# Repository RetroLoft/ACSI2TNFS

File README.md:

# ACSI2TNFS

A Raspberry Pi Pico 2 W on the **ACSI** (hard disk) port of an Atari. To the Atari it is
a hard disk; behind it are your network and a micro SD card.

It works with every 16-bit Atari that has an ACSI port: **ST, STE, Mega ST, Mega STE
and TT**. The Falcon has no ACSI port (it has SCSI), so ACSI2TNFS cannot be used there.

ACSI2TNFS gives the Atari:

- **Network drives:** folders on a **TNFS** server (a PC, a NAS, a Raspberry Pi) that
  the Atari sees as hard disk partitions, readable and writable.
- **SD card drives:** folders on a micro SD card in the adapter, also as hard disk
  partitions.
- **Internet:** with the STinG TCP/IP stack the Atari gets its own IP address on your
  Wi-Fi network: ping, FTP, web pages.
- **The right time:** the adapter gets the time from the internet and sets the Atari's
  clock.

All of these are optional: use only what you need. A small drive in the Pico's flash,
the **settings drive**, always comes with it: it holds the configuration program and the
tools.

> Status: working on real hardware: ST with TOS 1.02/1.04, Mega STE (TOS 2.06, HDDRIVER),
> TT (TOS 3.06, AHDI) and EmuTOS.

> [!IMPORTANT]
> ## MEGA STE AND TT: SET THE ADAPTER TO THE FIRST FREE ACSI ID
>
> **A new adapter uses ACSI id 6. On a Mega STE or a TT the machine does not see it there.**
>
> - **TT** (tested with AHDI): only ACSI id **0** is asked at start-up. Its own hard disk
>   is SCSI, so use **id 0**.
> - **Mega STE:** the internal hard disk adapter is on id 0, so use **id 1**. With
>   HDDRIVER also switch id 1 on in HDDRUTIL.
> - In general: the lowest id that no other device on the ACSI port uses.
>
> Set it with the USB console (key `0`–`7`) or `ACSITNFS.PRG` → *Config → More*, then
> restart the Atari. See [docs/ADAPTER.md](docs/ADAPTER.md#acsi-id).

## What you need

- The ACSI2TNFS board with a **Raspberry Pi Pico 2 W**: `v2` plugs straight into the
  Atari, `v2-cable` connects with a flat cable to a Lotharek DB19 adapter and has a
  pass-through connector. See [hardware/README.md](hardware/README.md).
- An Atari with an ACSI port and **TOS 1.02 or later**, or EmuTOS. TOS 1.0 does not
  see the adapter.
- For the network functions: a **2.4 GHz** Wi-Fi network.
- For SD card drives: a micro SD card, formatted on a PC as FAT32 (or exFAT).
- A USB cable for the Pico: it powers the adapter and gives a console on your PC.

## Getting started

1. **Firmware.** Download `acsi2tnfs.uf2` from
   [Releases](https://github.com/RetroLoft/ACSI2TNFS/releases). Hold the Pico's BOOTSEL
   button while you plug it into a PC, and copy the file onto the drive that appears.
   The Pico restarts and prepares its settings drive. (To build it yourself: see
   [docs/DEVELOPMENT.md](docs/DEVELOPMENT.md).)
2. **Connect** the adapter to the Atari's ACSI port and power the Pico over USB.
   Switch the Atari on. Without another hard disk you see `ACSI2TNFS v…` and
   `[OK] Drives installed: C:`.
3. **Show the settings drive on the desktop.** Select the floppy A: icon, *Options →
   Install Disk Drive*, letter `C`, *Install*, then *Options → Save Desktop*.
4. **Configure.** Start `ACSITNFS.PRG` on the settings drive: *Config* for Wi-Fi (network
   name, password, country) with *More* for the clock and the ACSI id, and the drive list
   for TNFS and SD drives (see below). *Save*; the Pico restarts and the Atari with it.

From then on the Atari boots with its drives and the right time.

## The settings drive

The first drive of the adapter lives in the Pico's flash (about 1 MB). Which letter it
gets depends on what else is connected:

- **No other hard disk:** the adapter boots with its own driver and the settings drive
  is **C:**, the boot drive, with your AUTO folder and DESKTOP.INF.
- **You already have a hard disk:** its driver boots and the adapter's drives follow
  after your own partitions. With a hard disk with C: and D:, the settings drive is E:.

On the settings drive:

| File | |
|---|---|
| `ACSITNFS.PRG` | the configuration program: Wi-Fi, TNFS and SD drives, network clock, ACSI id |
| `STINGINS.TOS` | installs STinG for internet on the Atari (below) |
| `NETCLOCK.PRG` | sets the Atari's clock from the network (for the AUTO folder, below) |
| `ACSI_NET.STX` | the STinG driver for the adapter (STINGINS.TOS installs it) |
| `README.TXT` | a short manual |

These files come with the firmware and are read-only. Your own files on the drive stay
when you update the firmware.

## Network drives (TNFS)

A TNFS drive shows a folder on a TNFS server as a hard disk partition. Setting up a TNFS
server is easy: [tnfsd](https://github.com/spectrumero/tnfsd) runs on Linux, macOS,
Windows and a Raspberry Pi; give it a folder and it serves that folder.

TNFS has no passwords and no encryption: run your server **only in your own network**
and do not open it to the internet.

In `ACSITNFS.PRG`, per drive: the server (name or IP address), the folder on the server
and the drive letter. More, and how writing works: [docs/TNFS.md](docs/TNFS.md).

## SD card drives

An SD drive shows a **folder** on the micro SD card in the adapter, e.g. `/ATARI`, as a
hard disk partition. It is not a disk image or a real partition: the adapter translates
the Atari's sector reads and writes into normal files on the card. Put the card in a PC
and you see the same files.

SD drives work without Wi-Fi. With a card in the adapter, TNFS drives also use it as a
write cache: writing to the network gets about six times faster.
More: [docs/SDCARD.md](docs/SDCARD.md).

## Drive letters and hard disk drivers

Next to the settings drive the adapter offers up to **three** TNFS or SD drives.
`ACSITNFS.PRG` has eight slots: the first three that are switched on are used.

Most TOS versions need a hard disk driver to use ACSI drives. Which one loads decides the
drive letters:

| Driver | Letters |
|---|---|
| **The adapter's own driver** (no other hard disk) | the settings drive is C:; TNFS and SD drives get the letters chosen in `ACSITNFS.PRG` (D: to P:). A letter that is taken gives the next free one |
| **AHDI** | assigns letters in order, after your own partitions; the letters in `ACSITNFS.PRG` are not used |
| **HDDRIVER** | assigns letters itself, also in order; HDDRUTIL has its own settings for letters and ACSI ids |
| **EmuTOS** | mounts the adapter with its own ACSI driver as C:, D:, … in order |

With AHDI, HDDRIVER and EmuTOS the adapter's driver does not load, so it does not set the
clock: use `NETCLOCK.PRG` (below). Details per driver and machine:
[docs/ADAPTER.md](docs/ADAPTER.md#booting).

## Internet on the Atari (STinG)

The adapter passes network traffic between the Atari and your Wi-Fi network. The Atari
runs the [STinG](https://github.com/th-otto/STinG) TCP/IP stack (freeware, for TOS); the
driver `ACSI_NET.STX` connects STinG to the adapter.

`STINGINS.TOS` on the settings drive installs everything (STinG 1.26 with TCP.STX 1.41).
Start it and answer its questions:

1. **The drive to install on:** your boot drive, almost always C: (it suggests it).
2. If STinG is already there: **1** changes only the network settings, **2** installs
   everything again. In doubt, choose 2.
3. **Atari IP address:** a **free** address in your network: not the adapter's own, and
   outside the range your router hands out (DHCP).
4. **Subnet mask:** almost always `255.255.255.0`.
5. **Gateway:** your router's IP address. On a Windows PC `ipconfig` shows it as
   *Default Gateway*.
6. **DNS server:** usually the router's address too.

The installer suggests mask, gateway and DNS from the adapter's own Wi-Fi settings.
Confirm, and it installs the files. Restart the Atari: STinG is on the network, without
XControl.

Test with `C:\STING\TOOLS\PING.PRG` to your router. Small STinG programs, e.g. a web
page viewer: [Network tools for the Atari ST](https://github.com/RetroLoft/atari-net-tools).
More, with what the installer writes and troubleshooting: [docs/NETWORK.md](docs/NETWORK.md).

## The clock (NETCLOCK.PRG)

With its own driver the adapter sets the Atari's clock at start-up (switch it on in
`ACSITNFS.PRG` → *Config → More*, with your time zone). With AHDI or HDDRIVER that driver
does not load: copy `NETCLOCK.PRG` into the AUTO folder of your boot drive. It waits for
the adapter's Wi-Fi and the time server (up to 30 s each, ESC skips) and sets the clock.

The time zone is a fixed offset from UTC: change it by hand for summer time.

## Limitations

- **8.3 file names only.** The Atari knows names of at most 8 characters plus a 3-letter
  extension. Longer names on the server or the card are shortened: `LONGFILENAME.TXT`
  shows as `LONGFILE.TXT`, or `LONGFI~1.TXT` when that name is taken. Names that start
  with a dot are hidden.
- **16 MB per drive.** Every TNFS and SD drive is a FAT16 partition of 16 MB, whatever
  the size of the folder behind it. A single file larger than that cannot be shown.
- **The room per drive can run out**, and folders then show up empty: see
  [Empty folders on a network or SD drive](#empty-folders-on-a-network-or-sd-drive).
- **Number of files:** at most 511 entries in the root of a drive and 254 in a folder;
  and about 2400 files and folders in all the folders the Atari has opened since its
  reset, shared by the drives (a drive that is used much takes what the others leave).
- **Changes on the server or the card** made by others (a PC) are seen after the Atari
  reads that folder again: after an Atari reset, or console `N`. Changes made by the
  Atari itself are seen at once.
- **Writing goes in two steps.** The Atari writes sectors; about a second after it
  stops, the adapter turns them into files on the server or card. A large file takes a
  few seconds to arrive on a TNFS server: wait a moment before you switch the adapter
  off.
- **Speed:** reading from a TNFS drive goes at network speed; writing is slower (much
  faster with an SD card as write cache). STinG reaches about 70 KB/s.
- **Drive letters stop at P:** (TOS knows 16 drives).
- **TOS 1.x with several drives:** put `FOLDR100.PRG` (from Atari's AHDI) in your AUTO
  folder, or TOS runs out of folder memory ("use FOLDR100.PRG").
- **Wi-Fi:** 2.4 GHz only (the Pico 2 W's radio).

## Empty folders on a network or SD drive

**Why it happens.** The Atari expects a hard disk with a FAT, a fixed table of where every
file lies. A network or SD drive has no such table: the adapter makes it up while you use
the drive. The first time the Atari opens a folder, the adapter reads that folder from
the server or the card and gives each file in it a place in the drive's 16 MB. That
place stays reserved until the drive starts afresh. The room for one session is limited:

- **16 MB of file space** per drive: every file in every folder you opened counts,
  whether you use it or not;
- **about 2400 files and folders**, shared by all network and SD drives;
- **only the part of the FAT that TOS has not read yet:** TOS keeps the FAT sectors it
  has read in memory, so the adapter cannot add new files there.

**What fills it up quickly**

- **Show Info** (*File → Show Info*) on a network or SD drive. To count the files and
  bytes, TOS opens **every folder** of the drive, down to the last subfolder. On a large
  server this uses up the room of the drive in one go, and every folder that did not
  fit is remembered by TOS as empty. Show Info on a single small folder is fine.
- Programs that ask for the free space of a drive: TOS then reads the whole FAT.
- Browsing through many folders full of large files (disk images, for example).

**What you see.** Folders you open after that are empty or show only part of their
files. The USB console (`n`, and the log) says "some skipped".

**What to do** depends on the hard disk driver:

| Driver | What happens | What you do |
|---|---|---|
| **The adapter's own driver** | after 2 seconds without disk activity the adapter starts the drive afresh and reports a media change; TOS reads the drive again | close the folder and open it again (TOS 2.06: or press Esc) |
| **HDDRIVER** | the same, once console `M` is on: the adapter then reports itself as a removable unit, and HDDRIVER asks for media changes | press `M` on the USB console once (it is stored), then reset the Atari once. Without `M`: reset the Atari |
| **AHDI** | nothing: AHDI does not hear of media changes | reset the Atari. **Leave `M` off:** with AHDI it makes TOS read the whole FAT again and again, and folders stay empty |
| **EmuTOS** (its built-in driver) | nothing: EmuTOS does not hear of media changes | reset the Atari (`M` makes no difference) |

A reset of the Atari always starts every drive afresh, with any driver. A single folder
whose files together are larger than 16 MB always shows only part of its files.

## Documentation

| | |
|---|---|
| [docs/TNFS.md](docs/TNFS.md) | Network drives: TNFS servers, writing, what to keep in mind |
| [docs/SDCARD.md](docs/SDCARD.md) | SD card drives and the write cache |
| [docs/NETWORK.md](docs/NETWORK.md) | Internet with STinG: the installer, IP address, programs, limits |
| [docs/ADAPTER.md](docs/ADAPTER.md) | ACSI id, booting, USB console, system files, troubleshooting |
| [hardware/README.md](hardware/README.md) | The boards `v2` and `v2-cable`, pin map, case |
| [docs/DEVELOPMENT.md](docs/DEVELOPMENT.md) | Building, repository layout, ACSI protocol, test tools |
| `ACSI_NET-ontwerp.md`, `project-notities.md` | Design and project notes (Dutch) |

## Credits

- Configuration program: the ACSI build of
  [SideTNFS-Config](https://github.com/RetroLoft/SideTNFS-Config).
- `ACSI_NET.STX` follows the structure of
  [USB_NET.STX (usbsting)](https://github.com/czietz/usbsting) by Roger Burrows and
  Christian Zietz (GPL-2+), and the frame bridge follows
  [PicoWifi](https://github.com/czietz/picowifi).
- STinG by Peter Rottengatter and Ronald Andersson (freeware); TCP.STX 1.41 by Christian
  Zietz ([chzsoft/sting](https://github.com/chzsoft/sting)). `STINGINS.TOS` carries
  them unchanged (`atari/install/sting/`).
- SD card: [FatFs](http://elm-chan.org/fsw/ff/) by ChaN.

## License

Copyright (C) 2025-2026 Frank Beentjes.

GNU General Public License, version 3 or (at your option) any later version: see
[LICENSE](LICENSE).

- `atari/sting/` (`ACSI_NET.STX`) contains code after USB_NET.STX and is GPL-2.0-or-later
  (`atari/sting/LICENSE`); `atari/sting/include/` holds headers from the STinG developer kit.
- The firmware is built with the Raspberry Pi Pico SDK (BSD-3-Clause), lwIP (BSD),
  FatFs (BSD-style, `third_party/fatfs`) and the `cyw43-driver` for the Wi-Fi chip, which
  Raspberry Pi licenses for use with its own microcontrollers only
  (`lib/cyw43-driver/LICENSE.RP` in the SDK).

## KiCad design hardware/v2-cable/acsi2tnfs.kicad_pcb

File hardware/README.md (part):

# ACSI2TNFS hardware

There are two boards with the same circuit and pin map, so one firmware fits both. Only
the way they connect to the Atari's ACSI port differs:

- **`v2`** plugs straight into the ACSI port, without a cable.
- **`v2-cable`** connects through a Lotharek DB19 adapter and a 20-wire flat cable, and
  can pass the ACSI bus on to another device, such as Lotharek's UltraSatan.

## Which one?

| | `v2` | `v2-cable` |
|---|---|---|
| Connection | plugs straight into the ACSI port | 20-wire flat cable to a Lotharek DB19 adapter in the ACSI port |
| Where it sits | upright on the back of the Atari, sticking out above it: leds, button and SD card in sight | loose on or behind the Atari |
| Pass-through | no | yes: a second header for another ACSI device, e.g. an UltraSatan |
| Case | none | a 3D-printable case (`v2-cable/case/`) |
| Special parts | 19 WAGO 243-131 pins for the DB19 | a Lotharek adapter (or build `acsi-adapter`) and a flat cable |

| `v2` | `v2-cable` |
|---|---|
|  |  |

*3D views from KiCad. Not every part has a 3D model (the SD socket and the button are
missing).*

## v2: straight into the ACSI port

The DB19 plug is part of the board: 19 loose pins soldered into the board take the place
of a DB19 plug (footprint `ACSI_DB19_Male_WAGO_243-131`). The board stands upright on
the back of the Atari, held by the port, and sticks out above it, so the leds, the
button and the micro SD card are in sight.

- **Pro:** no adapter and no cable needed.
- **Con:** you need the special pins: **WAGO 243-131** solder pins (1.0 mm pins in
  1.2 mm holes), 19 per board. For example from
  [Farnell](https://nl.farnell.com/en-NL/wago/243-131/solder-pin-2mm-pcb-terminal-block/dp/2643506)
  or [RS](https://nl.rs-online.com/web/p/terminal-block-accessories/2885173).
- No pass-through: the board takes the ACSI port.

## v2-cable: with a Lotharek adapter

The board lies loose on or behind the Atari and hangs on a Lotharek DB19 adapter through
a 20-wire flat cable. That adapter comes with Lotharek's
[UltraSatan](https://lotharek.pl/products.php?id=15): if you already have one, this is
the easiest way.

- **J1 "To ACSI"** takes the cable from the adapter. **J2 "ACSI pass-through"** carries
  the same signals on, e.g. to the UltraSatan, which then shares the bus with its own
  ACSI id.
- J1 and J2 are keyed box headers. Their pins are numbered **per row**: 1-10 along the
  row on the side of the key, 11-20 along the other row (footprint
  `IDC-Header_2x10_P2.54mm_Vertical_NR_PER_ROW`).
- So **pin n on the board is ACSI pin n**, because the adapter puts DB19 pins 1-10 on one
  row of its header and 11-19 on the other. This is **not** the usual IDC numbering
  (1 and 2 opposite each other): a standard 2x10 footprint would mix up the signals.
- The cable is a straight 20-wire flat cable with an IDC socket at each end, keyed the
  same way at both ends.

| Pin | Signal | Pin | Signal |
|---|---|---|---|
| 1-8 | DATA0-DATA7 | 11, 13, 15, 17 | GND |
| 9 | /CS | 12 | /RESET |
| 10 | /IRQ | 14 | /ACK |
| | | 16 | A1 |
| | | 18 | R/W |
| | | 19 | /DRQ |
| | | 20 | not used |

### No Lotharek adapter? Make one

`acsi-adapter` is the same adapter as a KiCad project: the DB19 of `v2` (the same special
pins) wired 1:1 to the IDC20 box header of `v2-cable`, pin 20 not connected. The box
header sits on the side of the wide DB19 row, like on Lotharek's adapter.

### The case

`v2-cable/case/` holds a 3D-printable case: `case.scad` (OpenSCAD) and ready STL files.

- **Bottom** with a flat front panel: the SD socket ends flush with it, the button
  sticks out about 1 mm, and the two 3 mm leds sit in holes. "ACSI2TNFS" is engraved in
  the corner.
- **Two lids:** `lid-vertical` for straight box headers (the rear left corner is open,
  with walls around the headers), `lid-right-angle` for angled box headers (openings in
  the rear wall).
- Two **M2.5 countersunk screws** (about 12 mm) from below, through the bottom and the
  board into plugs of the lid.
- Print the bottom as it is and the lid upside down (as in the STL files). No supports
  needed.
- **Assembly:** the SD socket and the button go through the front panel. Put the board
  in at the rear, slide it forward until the socket is flush with the panel, then screw
  it down. Trim the pins under the board to about 2.5 mm.
- The lid height is for a Pico on female headers (about 12.5 mm above the board).
  Heights and openings can be changed at the top of `case.scad`.

## Getting a board

Choose your version first, then whether you order the board ready-made or build it
yourself.

### Ordering it assembled

The boards are made for [JLCPCB](https://jlcpcb.com), which makes the board and solders
the SMD parts:

1. In KiCad, make the production files with the plugin
   [Fabrication Toolkit](https://github.com/bennymeg/Fabrication-Toolkit): it writes the
   Gerber zip, `bom.csv` and `positions.csv` into `production/`.
2. At JLCPCB upload the Gerber zip and switch on **PCB Assembly**, top side.
3. **Quantity:** 2, 5 or a multiple of 5. For 2 boards choose a **green** board: other
   colours start at 5.
4. Upload `bom.csv` and `positions.csv`. Parts without an LCSC number in the schematic
   are picked in the BOM step. **U1 and U2** must be the wide SOIC-20 version,
   **74LVC245ADW**, not the small TSSOP (APW).
5. **Check the placement preview:** the rotation of some parts is often wrong. For
   every IC, led and the SD socket the dot at pin 1 of the part must sit on the pin-1
   mark of the footprint; rotate the part in the preview where it does not.
6. The cheapest shipping works fine: boards usually arrive in the Netherlands from China
   in 10 to 14 days.

The through-hole parts (Pico headers, box headers or DB19 pins, button, 3 mm leds) are
easy to solder yourself afterwards, or ask JLCPCB to fit them too.

### Building it yourself

All SMD parts are on the top side and have a pin pitch of 1.1 mm or more, so a
**hotplate** works well:

1. **SMD parts on the hotplate.** Put a tiny dot of solder paste on each pad: a dot is
   enough to solder a pin to its pad. With too much paste neighbouring pins bridge. A
   stencil is not needed.
2. Place the parts with tweezers, heat the board until the paste flows, let it cool.
3. **Through-hole parts** with a normal soldering iron: Pico headers, box headers or
   DB19 pins, button, leds.

Plenty of videos show hotplate soldering. Useful tools: reading glasses or a magnifier,
good light, tweezers, and a **toothpick**: it is not magnetic and good for moving paste
and parts.

### Parts

| Ref | Part | Package | Notes |
|---|---|---|---|
| A1 | Raspberry Pi Pico 2 W | module | on female headers (socket) or soldered |
| U1, U2 | 74LVC245ADW | SOIC-20W | wide SOIC, not TSSOP |
| U3 | 74LS07 | SOIC-14 | |
| Card1 | TF-01A micro SD socket (LCSC C91145) | SMD | push-push |
| R1, R2, R5-R8 | 10k | 0805 | |
| R3, R4 | 470 Ω | 0805 | led resistors |
| C1, C5, C7 | 10 µF | 0805 | |
| C2, C3, C4, C6 | 100 nF | 0805 | |
| SW1 | 6 mm tactile switch, right angle (Alps SKHH footprint) | THT | |
| D1, D2 (`v2`) | led 3 mm: D1 yellow, D2 blue | THT | bent forward |
| D1, D2 / D3, D4 (`v2-cable`) | led 0805 / led 3 mm: D1/D3 yellow, D2/D4 blue | SMD / THT | fit **either** D1 **or** D3, and D2 **or** D4 |
| J1 (`v2`) | 19 × WAGO 243-131 | THT | the DB19 plug |
| J1, J2 (`v2-cable`) | 2x10 box header, 2.54 mm, straight or right angle | THT | the lid of the case depends on it |

## Both boards

- **Raspberry Pi Pico 2 W** on pin headers. The Pico powers the board from USB; the
  ACSI port has no supply pin.
- **U1** 74LVC245: data bus D0-D7, direction (DIR) and enable (/OE) from the Pico.
  **U2** 74LVC245: /CS, /RESET, /ACK, A1 and R/W to the Pico, fixed direction.
  **U3** 74LS07: /IRQ and /DRQ as open-collector outputs.
- **Card1:** micro SD socket on SPI0, with card detect.
- **SW1:** button (hidden mode on/off). **Leds:** D1 disk activity, D2 status (on, blinking
  while hidden); on `v2-cable` D3 and D4 when the 3 mm leds are fitted.

### Design rules learnt the hard way

The Atari's floppy controller shares the ACSI data bus and the /IRQ line, so the board
must keep off them when it is not talking:

- **No pull-ups on /IRQ and /DRQ** to the board's own supply: without USB that supply is
  0 V and the resistors pull the lines low, which upsets the floppy drive. The Atari has
  its own pull-ups.
- **10k pull-up on /OE of U1** (R5): the data bus buffer stays off while the Pico is not
  running (power-up, reset, BOOTSEL).
- **10k pull-ups on the 74LS07 inputs** (R6, R7): a Pico in reset pulls its pins low,
  which would otherwise assert /IRQ and /DRQ.

### Pin map (v2 and v2-cable)

| Pico | Signal | Pico | Signal |
|---|---|---|---|
| GP0 | led D1 (disk activity) | GP16 | /CS |
| GP1 | SD card detect | GP17 | /RESET |
| GP2-GP5 | SD card: CLK, MOSI, MISO, CS | GP18 | /ACK |
| GP6-GP13 | DATA7 ... DATA0 (reversed order) | GP19 | A1 |
| GP14 | DIR of U1 | GP20 | R/W |
| GP15 | /OE of U1 | GP21 | /IRQ (via U3, low = active) |
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
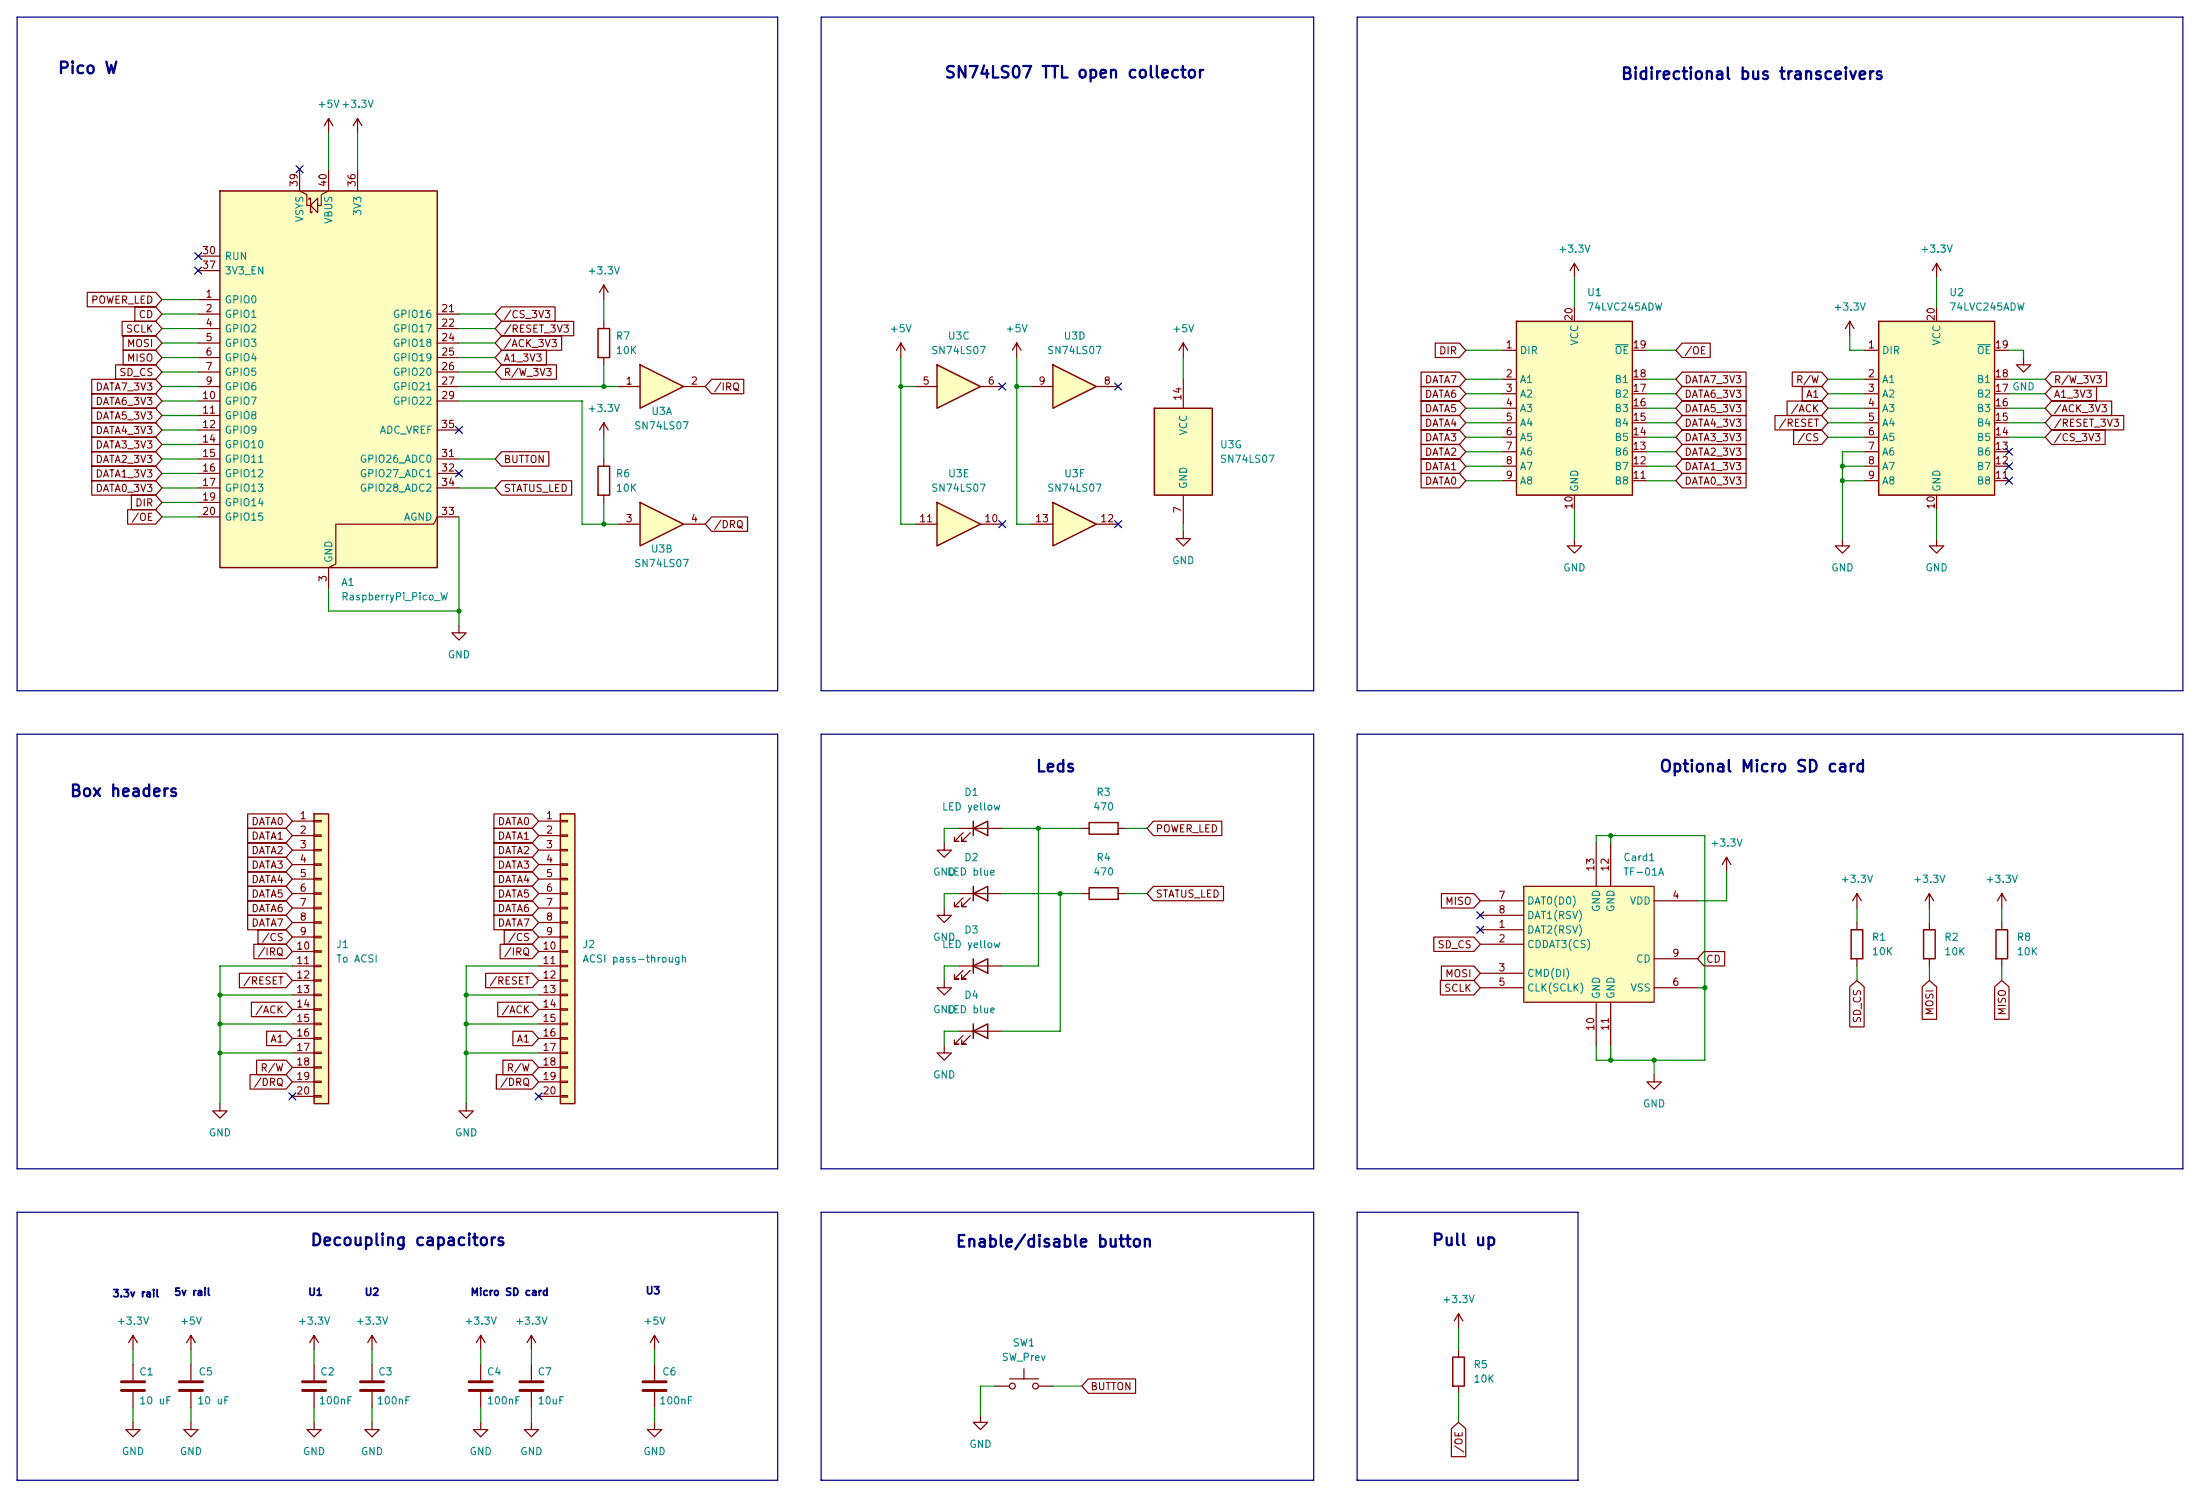
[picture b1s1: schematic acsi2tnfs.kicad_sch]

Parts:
A1: RaspberryPi_Pico_W; RaspberryPi_Pico_Common_THT
C1, C5: 10 uF; C_0805_2012Metric
C2, C3, C4, C6: 100nF; C_0805_2012Metric
C7: 10uF; C_0805_2012Metric
Card1: TF-01A; TF-SMD_TF-01A; MPN TF-01A; LCSC Part C91145
D1: LED yellow; LED_0805_2012Metric
D2: LED blue; LED_0805_2012Metric
D3: LED yellow; LED_D3.0mm
D4: LED blue; LED_D3.0mm
J1: To ACSI; IDC-Header_2x10_P2.54mm_Vertical_NR_PER_ROW
J2: ACSI pass-through; IDC-Header_2x10_P2.54mm_Vertical_NR_PER_ROW
R1, R2, R5, R6, R7, R8: 10K; R_0805_2012Metric
R3, R4: 470; R_0805_2012Metric
SW1: SW_Prev; SW_Tactile_SKHH_Angled
U1, U2: 74LVC245ADW; SOIC-20W_7.5x15.4mm_P1.27mm
U3: SN74LS07; SOIC-14_3.9x8.7mm_P1.27mm

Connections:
+3.3V: A1.36 (3V3), C1.1, C2.1, C3.1, C4.1, C7.1, Card1.4 (VDD), R1.1, R2.1, R5.1, R6.1, R7.1, R8.1, U1.20 (VCC), U2.1 (DIR), U2.20 (VCC)
+5V: A1.40 (VBUS), C5.1, C6.1, U3.5, U3.9, U3.11, U3.13, U3.14 (VCC)
A1: J1.16, J2.16, U2.3 (A2)
A1_3V3: A1.25 (GPIO19), U2.17 (B2)
BUTTON: A1.31 (GPIO26_ADC0), SW1.2
CD: A1.2 (GPIO1), Card1.9 (CD)
DATA0: J1.1, J2.1, U1.9 (A8)
DATA0_3V3: A1.17 (GPIO13), U1.11 (B8)
DATA1: J1.2, J2.2, U1.8 (A7)
DATA1_3V3: A1.16 (GPIO12), U1.12 (B7)
DATA2: J1.3, J2.3, U1.7 (A6)
DATA2_3V3: A1.15 (GPIO11), U1.13 (B6)
DATA3: J1.4, J2.4, U1.6 (A5)
DATA3_3V3: A1.14 (GPIO10), U1.14 (B5)
DATA4: J1.5, J2.5, U1.5 (A4)
DATA4_3V3: A1.12 (GPIO9), U1.15 (B4)
DATA5: J1.6, J2.6, U1.4 (A3)
DATA5_3V3: A1.11 (GPIO8), U1.16 (B3)
DATA6: J1.7, J2.7, U1.3 (A2)
DATA6_3V3: A1.10 (GPIO7), U1.17 (B2)
DATA7: J1.8, J2.8, U1.2 (A1)
DATA7_3V3: A1.9 (GPIO6), U1.18 (B1)
DIR: A1.19 (GPIO14), U1.1 (DIR)
GND: A1.3 (GND), A1.8 (GND), A1.13 (GND), A1.18 (GND), A1.23 (GND), A1.28 (GND), A1.33 (AGND), A1.38 (GND), C1.2, C2.2, C3.2, C4.2, C5.2, C6.2, C7.2, Card1.6 (VSS), Card1.10 (GND), Card1.11 (GND), Card1.12 (GND), Card1.13 (GND), D1.1 (K), D2.1 (K), D3.1 (K), D4.1 (K), J1.11, J1.13, J1.15, J1.17, J2.11, J2.13, J2.15, J2.17, SW1.1, U1.10 (GND), U2.7 (A6), U2.8 (A7), U2.9 (A8), U2.10 (GND), U2.19 (~OE), U3.7 (GND)
MISO: A1.6 (GPIO4), Card1.7 (DAT0(D0)), R8.2
MOSI: A1.5 (GPIO3), Card1.3 (CMD(DI)), R2.2
unnamed: A1.27 (GPIO21), R7.2, U3.1
unnamed: A1.29 (GPIO22), R6.2, U3.3
unnamed: D1.2 (A), D3.2 (A), R3.1
unnamed: D2.2 (A), D4.2 (A), R4.1
POWER_LED: A1.1 (GPIO0), R3.2
R/W: J1.18, J2.18, U2.2 (A1)
R/W_3V3: A1.26 (GPIO20), U2.18 (B1)
SCLK: A1.4 (GPIO2), Card1.5 (CLK(SCLK))
SD_CS: A1.7 (GPIO5), Card1.2 (CDDAT3(CS)), R1.2
STATUS_LED: A1.34 (GPIO28_ADC2), R4.2
/ACK: J1.14, J2.14, U2.4 (A3)
/ACK_3V3: A1.24 (GPIO18), U2.16 (B3)
/CS: J1.9, J2.9, U2.6 (A5)
/CS_3V3: A1.21 (GPIO16), U2.14 (B5)
/DRQ: J1.19, J2.19, U3.4
/IRQ: J1.10, J2.10, U3.2
/OE: A1.20 (GPIO15), R5.2, U1.19 (~OE)
/RESET: J1.12, J2.12, U2.5 (A4)
/RESET_3V3: A1.22 (GPIO17), U2.15 (B4)

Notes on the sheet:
Leds
Decoupling capacitors
Micro SD card
Enable/disable button
Bidirectional bus transceivers
SN74LS07 TTL open collector
Box headers
Pull up
5v rail
3.3v rail
Optional Micro SD card
Pico W

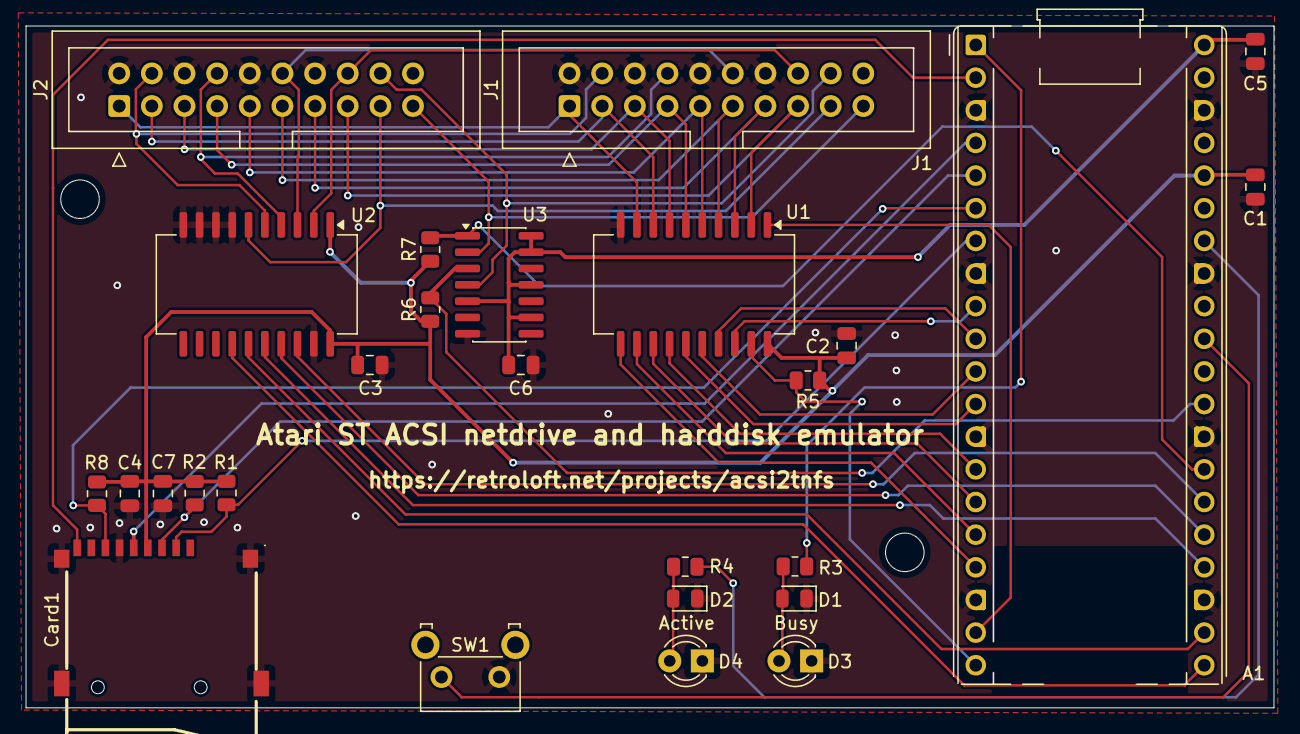
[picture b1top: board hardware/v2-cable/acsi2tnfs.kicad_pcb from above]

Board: 2 copper layers, 97.1 x 53.1 mm, 27 parts (0 on the bottom side), 45 nets.

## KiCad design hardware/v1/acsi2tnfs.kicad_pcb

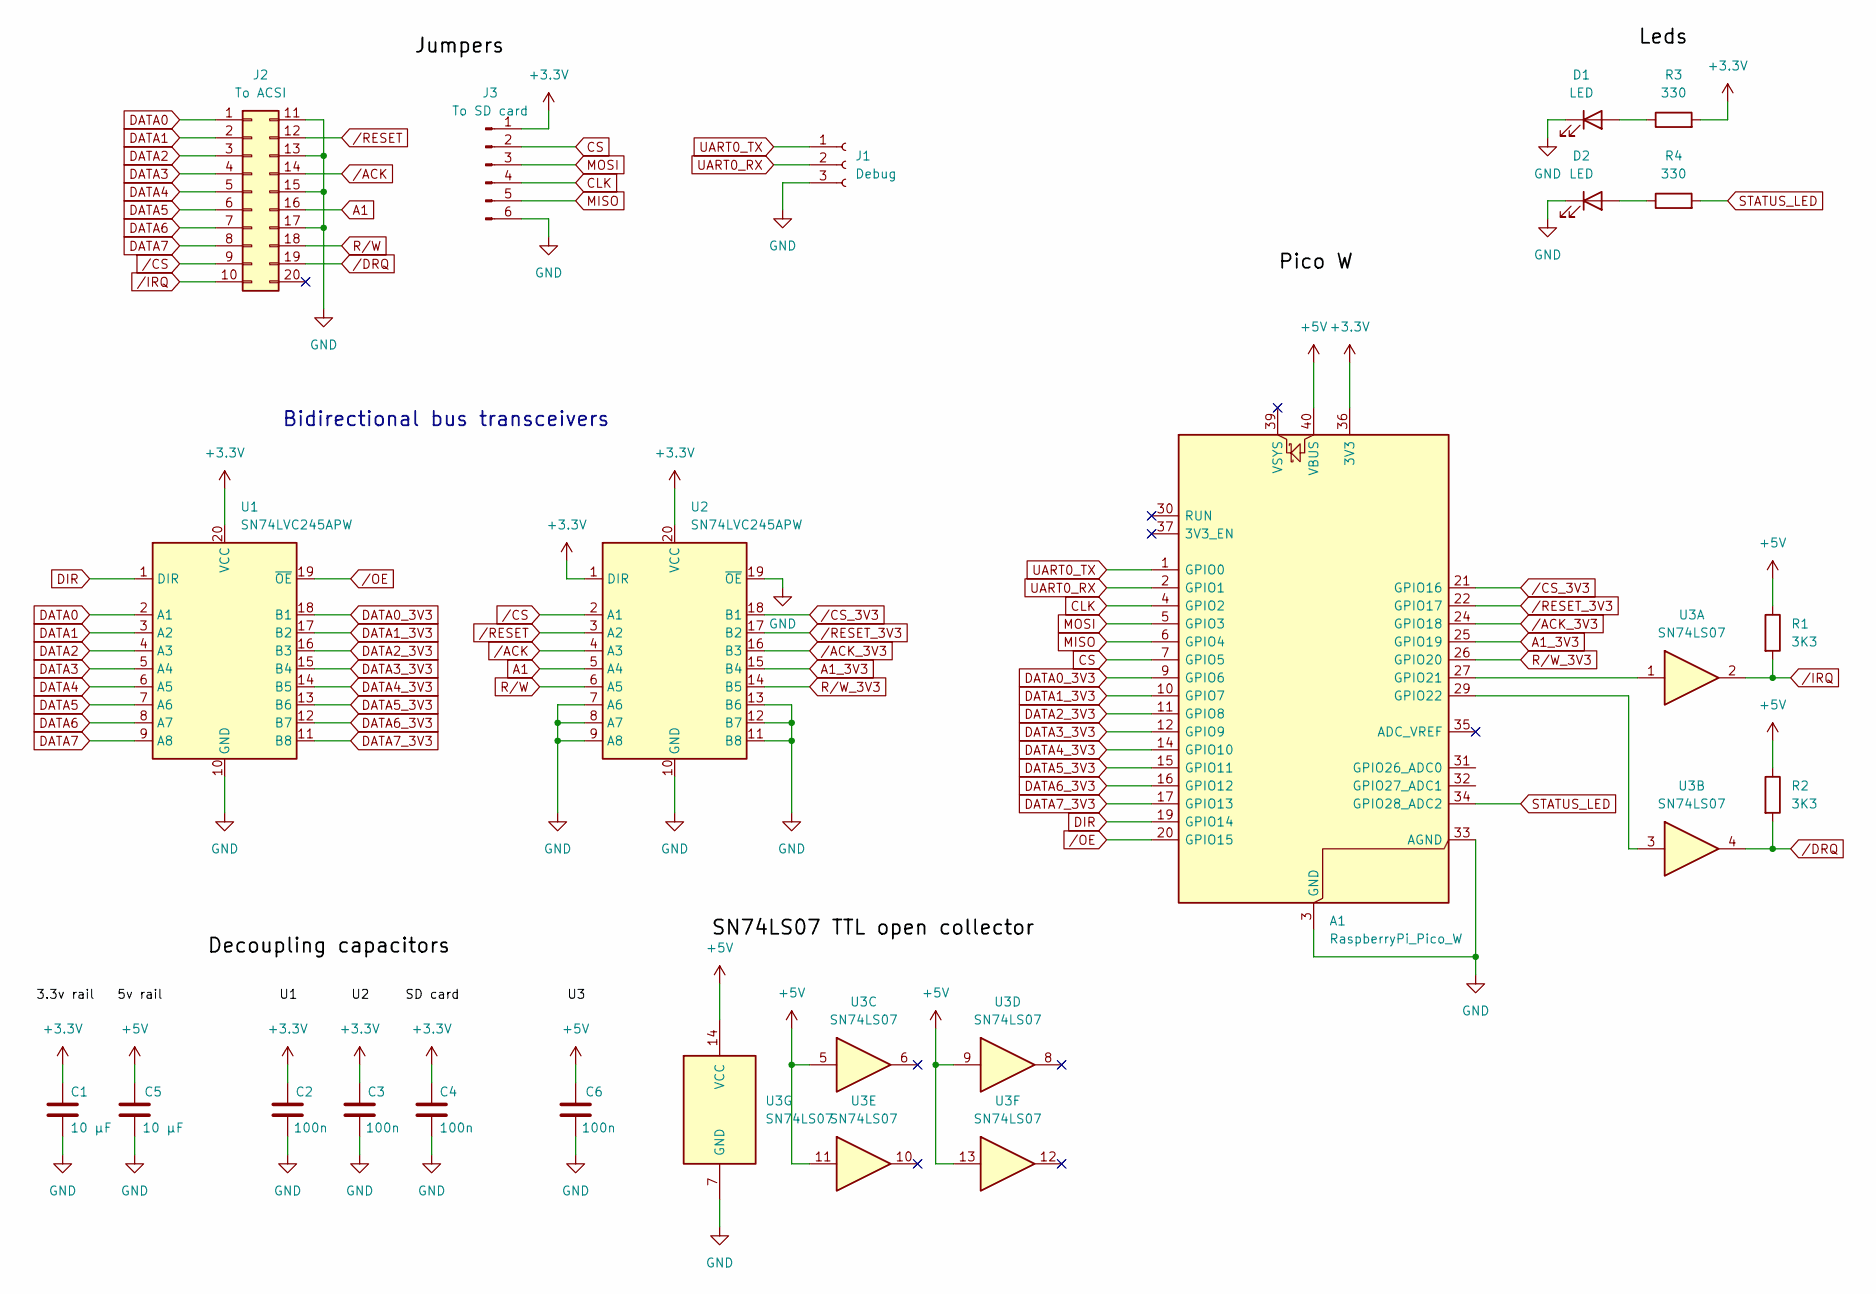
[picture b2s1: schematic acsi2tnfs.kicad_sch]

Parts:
A1: RaspberryPi_Pico_W; RaspberryPi_Pico_Common_THT
C1, C5: 10 µF; C_0805_2012Metric
C2, C3, C4, C6: 100n; C_0805_2012Metric
D1, D2: LED; LED_0805_2012Metric
J1: Debug; PinHeader_1x03_P2.54mm_Vertical
J2: To ACSI; PinHeader_2x10_P2.54mm_Vertical_NR_PER_ROW
J3: To SD card; PinHeader_1x06_P2.54mm_Vertical
R1, R2: 3K3; R_0805_2012Metric
R3, R4: 330; R_0805_2012Metric
U1, U2: SN74LVC245APW; SOIC-20W_7.5x15.4mm_P1.27mm
U3: SN74LS07; SOIC-14_3.9x8.7mm_P1.27mm

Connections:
+3.3V: A1.36 (3V3), C1.1, C2.1, C3.1, C4.1, J3.1, R3.2, U1.20 (VCC), U2.1 (DIR), U2.20 (VCC)
+5V: A1.40 (VBUS), C5.1, C6.1, R1.1, R2.1, U3.5, U3.9, U3.11, U3.13, U3.14 (VCC)
A1: J2.16, U2.5 (A4)
A1_3V3: A1.25 (GPIO19), U2.15 (B4)
CLK: A1.4 (GPIO2), J3.4
CS: A1.7 (GPIO5), J3.2
DATA0: J2.1, U1.2 (A1)
DATA0_3V3: A1.9 (GPIO6), U1.18 (B1)
DATA1: J2.2, U1.3 (A2)
DATA1_3V3: A1.10 (GPIO7), U1.17 (B2)
DATA2: J2.3, U1.4 (A3)
DATA2_3V3: A1.11 (GPIO8), U1.16 (B3)
DATA3: J2.4, U1.5 (A4)
DATA3_3V3: A1.12 (GPIO9), U1.15 (B4)
DATA4: J2.5, U1.6 (A5)
DATA4_3V3: A1.14 (GPIO10), U1.14 (B5)
DATA5: J2.6, U1.7 (A6)
DATA5_3V3: A1.15 (GPIO11), U1.13 (B6)
DATA6: J2.7, U1.8 (A7)
DATA6_3V3: A1.16 (GPIO12), U1.12 (B7)
DATA7: J2.8, U1.9 (A8)
DATA7_3V3: A1.17 (GPIO13), U1.11 (B8)
DIR: A1.19 (GPIO14), U1.1 (DIR)
GND: A1.3 (GND), A1.8 (GND), A1.13 (GND), A1.18 (GND), A1.23 (GND), A1.28 (GND), A1.33 (AGND), A1.38 (GND), C1.2, C2.2, C3.2, C4.2, C5.2, C6.2, D1.1 (K), D2.1 (K), J1.3, J2.11, J2.13, J2.15, J2.17, J3.6, U1.10 (GND), U2.7 (A6), U2.8 (A7), U2.9 (A8), U2.10 (GND), U2.11 (B8), U2.12 (B7), U2.13 (B6), U2.19 (~OE), U3.7 (GND)
MISO: A1.6 (GPIO4), J3.5
MOSI: A1.5 (GPIO3), J3.3
unnamed: A1.27 (GPIO21), U3.1
unnamed: A1.29 (GPIO22), U3.3
unnamed: D1.2 (A), R3.1
unnamed: D2.2 (A), R4.1
R/W: J2.18, U2.6 (A5)
R/W_3V3: A1.26 (GPIO20), U2.14 (B5)
STATUS_LED: A1.34 (GPIO28_ADC2), R4.2
UART0_RX: A1.2 (GPIO1), J1.2
UART0_TX: A1.1 (GPIO0), J1.1
/ACK: J2.14, U2.4 (A3)
/ACK_3V3: A1.24 (GPIO18), U2.16 (B3)
/CS: J2.9, U2.2 (A1)
/CS_3V3: A1.21 (GPIO16), U2.18 (B1)
/DRQ: J2.19, R2.2, U3.4
/IRQ: J2.10, R1.2, U3.2
/OE: A1.20 (GPIO15), U1.19 (~OE)
/RESET: J2.12, U2.3 (A2)
/RESET_3V3: A1.22 (GPIO17), U2.17 (B2)

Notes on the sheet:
Bidirectional bus transceivers

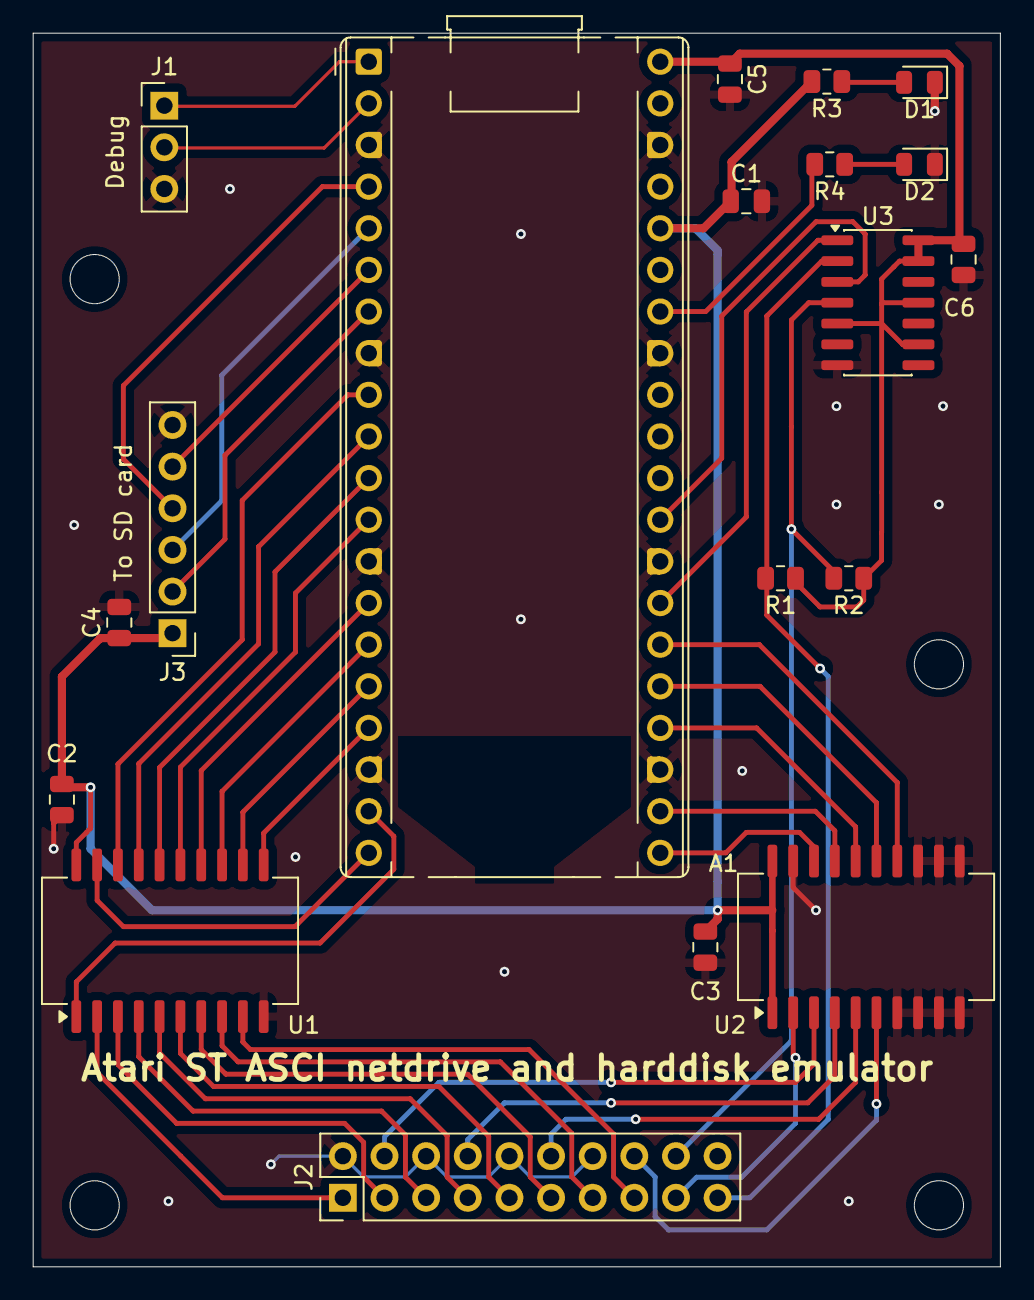
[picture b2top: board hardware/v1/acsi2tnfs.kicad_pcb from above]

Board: 2 copper layers, 59.0 x 75.2 mm, 19 parts (0 on the bottom side), 44 nets.

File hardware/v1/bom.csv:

Id;Aanduiding;Footprint;Hoeveelheid;Orientatie;Leverancier en ref
1;U1,U2;SOIC-20W_7.5x15.4mm_P1.27mm;2;SN74LVC245APW;
2;J1;PinHeader_1x03_P2.54mm_Vertical;1;Debug;
3;R4,R3;R_0805_2012Metric;2;330;
4;J2;PinHeader_2x10_P2.54mm_Vertical_NR_PER_ROW;1;To ACSI;
5;J3;PinHeader_1x06_P2.54mm_Vertical;1;To SD card;
6;D1,D2;LED_0805_2012Metric;2;LED;
7;C6,C3,C4,C2;C_0805_2012Metric;4;100n;
8;U3;SOIC-14_3.9x8.7mm_P1.27mm;1;SN74LS07;
9;C1,C5;C_0805_2012Metric;2;10 µF;
10;A1;RaspberryPi_Pico_Common_THT;1;RaspberryPi_Pico_W;
11;R2,R1;R_0805_2012Metric;2;3K3;

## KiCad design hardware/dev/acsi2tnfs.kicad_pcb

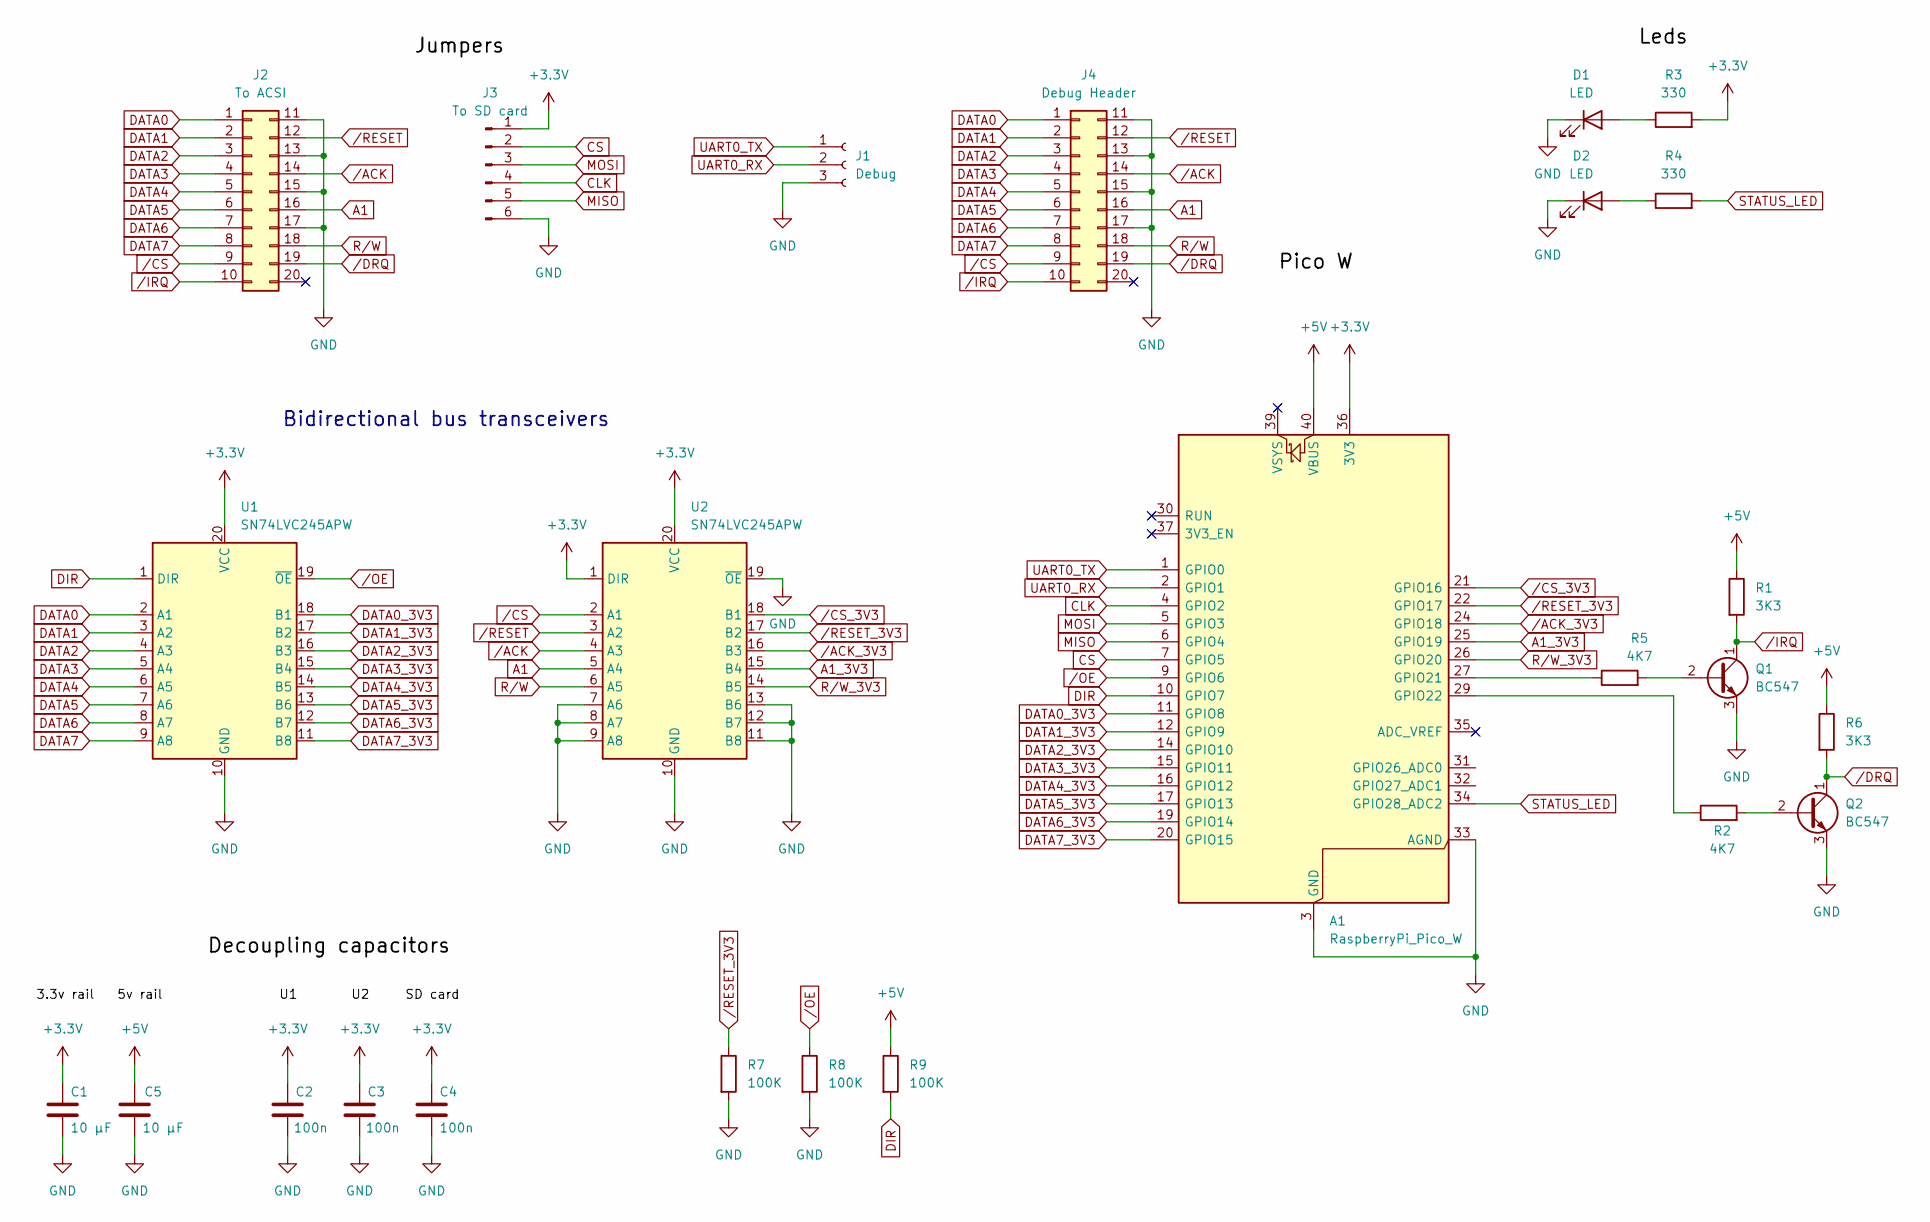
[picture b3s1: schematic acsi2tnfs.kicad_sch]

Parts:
A1: RaspberryPi_Pico_W; RaspberryPi_Pico_Common_THT
C1, C5: 10 µF; C_0805_2012Metric
C2, C3, C4: 100n; C_0805_2012Metric
D1, D2: LED; LED_0805_2012Metric
J1: Debug; PinHeader_1x03_P2.54mm_Vertical
J2: To ACSI; PinHeader_2x10_P2.54mm_Vertical_NR_PER_ROW
J3: To SD card; PinHeader_1x06_P2.54mm_Vertical
J4: Debug Header; PinHeader_2x10_P2.54mm_Vertical_NR_PER_ROW
Q1, Q2: BC547; TO-92_Inline
R1, R6: 3K3; R_0805_2012Metric
R2, R5: 4K7; R_0805_2012Metric
R3, R4: 330; R_0805_2012Metric
R7, R8, R9: 100K; R_0805_2012Metric
U1, U2: SN74LVC245APW; SOIC-20W_7.5x15.4mm_P1.27mm

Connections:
+3.3V: A1.36 (3V3), C1.1, C2.1, C3.1, C4.1, J3.1, R3.2, U1.20 (VCC), U2.1 (DIR), U2.20 (VCC)
+5V: A1.40 (VBUS), C5.1, R1.1, R6.1, R9.1
A1: J2.16, J4.16, U2.5 (A4)
A1_3V3: A1.25 (GPIO19), U2.15 (B4)
CLK: A1.4 (GPIO2), J3.4
CS: A1.7 (GPIO5), J3.2
DATA0: J2.1, J4.1, U1.2 (A1)
DATA0_3V3: A1.11 (GPIO8), U1.18 (B1)
DATA1: J2.2, J4.2, U1.3 (A2)
DATA1_3V3: A1.12 (GPIO9), U1.17 (B2)
DATA2: J2.3, J4.3, U1.4 (A3)
DATA2_3V3: A1.14 (GPIO10), U1.16 (B3)
DATA3: J2.4, J4.4, U1.5 (A4)
DATA3_3V3: A1.15 (GPIO11), U1.15 (B4)
DATA4: J2.5, J4.5, U1.6 (A5)
DATA4_3V3: A1.16 (GPIO12), U1.14 (B5)
DATA5: J2.6, J4.6, U1.7 (A6)
DATA5_3V3: A1.17 (GPIO13), U1.13 (B6)
DATA6: J2.7, J4.7, U1.8 (A7)
DATA6_3V3: A1.19 (GPIO14), U1.12 (B7)
DATA7: J2.8, J4.8, U1.9 (A8)
DATA7_3V3: A1.20 (GPIO15), U1.11 (B8)
DIR: A1.10 (GPIO7), R9.2, U1.1 (DIR)
GND: A1.3 (GND), A1.8 (GND), A1.13 (GND), A1.18 (GND), A1.23 (GND), A1.28 (GND), A1.33 (AGND), A1.38 (GND), C1.2, C2.2, C3.2, C4.2, C5.2, D1.1 (K), D2.1 (K), J1.3, J2.11, J2.13, J2.15, J2.17, J3.6, J4.11, J4.13, J4.15, J4.17, Q1.3 (E), Q2.3 (E), R7.2, R8.2, U1.10 (GND), U2.7 (A6), U2.8 (A7), U2.9 (A8), U2.10 (GND), U2.11 (B8), U2.12 (B7), U2.13 (B6), U2.19 (~OE)
MISO: A1.6 (GPIO4), J3.5
MOSI: A1.5 (GPIO3), J3.3
unnamed: A1.27 (GPIO21), R5.1
unnamed: A1.29 (GPIO22), R2.1
unnamed: D1.2 (A), R3.1
unnamed: D2.2 (A), R4.1
unnamed: Q1.2 (B), R5.2
unnamed: Q2.2 (B), R2.2
R/W: J2.18, J4.18, U2.6 (A5)
R/W_3V3: A1.26 (GPIO20), U2.14 (B5)
STATUS_LED: A1.34 (GPIO28_ADC2), R4.2
UART0_RX: A1.2 (GPIO1), J1.2
UART0_TX: A1.1 (GPIO0), J1.1
/ACK: J2.14, J4.14, U2.4 (A3)
/ACK_3V3: A1.24 (GPIO18), U2.16 (B3)
/CS: J2.9, J4.9, U2.2 (A1)
/CS_3V3: A1.21 (GPIO16), U2.18 (B1)
/DRQ: J2.19, J4.19, Q2.1 (C), R6.2
/IRQ: J2.10, J4.10, Q1.1 (C), R1.2
/OE: A1.9 (GPIO6), R8.1, U1.19 (~OE)
/RESET: J2.12, J4.12, U2.3 (A2)
/RESET_3V3: A1.22 (GPIO17), R7.1, U2.17 (B2)

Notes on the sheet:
Bidirectional bus transceivers
